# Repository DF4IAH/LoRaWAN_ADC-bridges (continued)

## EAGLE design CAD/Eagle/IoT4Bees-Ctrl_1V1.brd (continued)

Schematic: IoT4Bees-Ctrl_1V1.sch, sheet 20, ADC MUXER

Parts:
C2001, C2011, C2012, C2021, C2022, C2061, C2062, C2071, C2072: 100nF; C0402
L2011, L2012, L2021, L2022, L2061, L2062, L2071, L2072: 10uH; L0603
R2001, R2002, R2003, R2004: 0R; R0402
R2005, R2006: 22kR; R0402
R2011, R2012, R2021, R2022, R2061, R2062, R2071, R2072, R2090, R2091: 47R; R0402
U2011, U2012, U2021, U2022: TS5A23166; R-PDSO-G8

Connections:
+3V3_BRIDGE_PWR: C2001.1, R2005.2, R2006.2, U2011.8, U2012.8, U2021.8, U2022.8; also elsewhere on the board
ADC_MUX1_P1: C2011.1, L2011.1, R2001.2, U2011.1
ADC_MUX1_P1_L: L2011.2, R2011.1
ADC_MUX1_P5: C2061.1, L2061.1, R2002.2, U2011.5
ADC_MUX1_P5_L: L2061.2, R2061.1
ADC_MUX2_P1: C2021.1, L2021.2, R2003.1, U2021.1
ADC_MUX2_P1_L: L2021.1, R2021.2
ADC_MUX2_P5: C2071.1, L2071.2, R2004.1, U2021.5
ADC_MUX2_P5_L: L2071.1, R2071.2
ADC_MUX3_P1: C2012.1, L2012.1, U2012.1
ADC_MUX3_P1_L: L2012.2, R2012.1
ADC_MUX3_P5: C2062.1, L2062.1, U2012.5
ADC_MUX3_P5_L: L2062.2, R2062.1
ADC_MUX4_P1: C2022.1, L2022.2, U2022.1
ADC_MUX4_P1_L: L2022.1, R2022.2
ADC_MUX4_P5: C2072.1, L2072.2, U2022.5
ADC_MUX4_P5_L: L2072.1, R2072.2
ADC_MUX_GROUP0: R2090.2, U2011.3, U2011.7, U2021.3, U2021.7
ADC_MUX_GROUP1: R2091.2, U2012.3, U2012.7, U2022.3, U2022.7
ADC_VIN1N: R2002.1, U2011.6, U2012.6; also elsewhere on the board
ADC_VIN1P: R2001.1, R2005.1, U2011.2, U2012.2; also elsewhere on the board
ADC_VIN2N: R2004.2, U2021.6, U2022.6; also elsewhere on the board
ADC_VIN2P: R2003.2, R2006.1, U2021.2, U2022.2; also elsewhere on the board
BRIDGE_N1: R2061.2; also elsewhere on the board
BRIDGE_N2: R2071.1; also elsewhere on the board
BRIDGE_N3: R2062.2; also elsewhere on the board
BRIDGE_N4: R2072.1; also elsewhere on the board
BRIDGE_P1: R2011.2; also elsewhere on the board
BRIDGE_P2: R2021.1; also elsewhere on the board
BRIDGE_P3: R2012.2; also elsewhere on the board
BRIDGE_P4: R2022.1; also elsewhere on the board
GND: C2001.2, C2011.2, C2012.2, C2021.2, C2022.2, C2061.2, C2062.2, C2071.2, C2072.2, U2011.4, U2012.4, U2021.4, U2022.4; also elsewhere on the board
PH0: R2090.1; also elsewhere on the board
PH1: R2091.1; also elsewhere on the board

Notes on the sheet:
ADC MUXER for bridge input lines
ADC MUXER
GPIO_MUXG0_EN
GPIO_MUXG1_EN

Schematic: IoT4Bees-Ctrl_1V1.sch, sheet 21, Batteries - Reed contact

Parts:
BUZZER+: CUI Inc. CEB-44D06; SMD2,54-5,08
BUZZER-: CUI Inc. CEB-44D06; SMD2,54-5,08
C2111, C2132: 10pF; C0402
C2121: 10nF; C0402
L2111: 10uH; L0603
R2121: 1kR; R0402
S2131: REED-SWITCH-MK6-10; MK6-10
VIN+: 6V; SMD2,54-5,08
VIN-: 6V; SMD2,54-5,08

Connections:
+3V3: S2131.2; also elsewhere on the board
BUZZER: BUZZER+.1, R2121.1
GND: BUZZER-.1, C2111.2, C2121.2, C2132.2, VIN-.1; also elsewhere on the board
PA0: C2132.1, S2131.1; also elsewhere on the board
PB8: C2121.1, R2121.2; also elsewhere on the board
VBAT: L2111.2, VIN+.1
VBAT_L: C2111.1, L2111.1; also elsewhere on the board

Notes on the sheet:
Batteries connector
Batteries connector Reed contact
Reed contact
MCU_REED
Buzzer connector
TIM16_CH1_BUZZER

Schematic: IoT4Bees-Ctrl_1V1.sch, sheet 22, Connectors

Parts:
X2211, X2212: PHOENIX_1990067_1X8X2MM50_PTSA-0-5
X2251, X2252, X2253: HEADER-2X5_1MM27; 2X05_1MM27

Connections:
+3V3: X2251.3, X2251.9; also elsewhere on the board
+3V3_BRIDGE_PWR: X2211.1, X2211.5, X2212.1, X2212.5, X2251.4; also elsewhere on the board
+3V3_I2C1_PWR: X2251.6; also elsewhere on the board
+3V3_SPI3_PWR: X2251.5; also elsewhere on the board
+BAT_VOLTAGE_PWR: X2251.2; also elsewhere on the board
BRIDGE_N1: X2211.3; also elsewhere on the board
BRIDGE_N2: X2211.7; also elsewhere on the board
BRIDGE_N3: X2212.3; also elsewhere on the board
BRIDGE_N4: X2212.7; also elsewhere on the board
BRIDGE_P1: X2211.2; also elsewhere on the board
BRIDGE_P2: X2211.6; also elsewhere on the board
BRIDGE_P3: X2212.2; also elsewhere on the board
BRIDGE_P4: X2212.6; also elsewhere on the board
GND: X2211.4, X2211.8, X2212.4, X2212.8, X2251.10, X2252.10, X2253.10; also elsewhere on the board
PA1: X2253.8; also elsewhere on the board
PA2: X2253.9; also elsewhere on the board
PA5: X2252.9; also elsewhere on the board
PA6: X2252.8, X2253.7; also elsewhere on the board
PA7: X2252.7; also elsewhere on the board
PA9: X2252.2; also elsewhere on the board
PA10: X2252.1; also elsewhere on the board
PB1: X2253.5; also elsewhere on the board
PB10: X2253.1; also elsewhere on the board
PB11: X2253.2; also elsewhere on the board
PB13: X2253.6; also elsewhere on the board
PC0: X2253.4; also elsewhere on the board
PC1: X2253.3; also elsewhere on the board
PC2: X2252.3; also elsewhere on the board
PC3: X2252.4; also elsewhere on the board
PC4: X2252.5; also elsewhere on the board
PC13: X2252.6; also elsewhere on the board
PEXPA_P1_6_R: X2251.7; also elsewhere on the board
PEXPA_P1_7_R: X2251.8; also elsewhere on the board
VBAT_L: X2251.1; also elsewhere on the board

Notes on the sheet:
Connectors / Headers
BOARD_WKUP
Bridge Input Connectors
Expansion Connectors
SPI1_CLK
SPI1_MOSI
SPI1_MISO
SPI1_EXP_SEL
GPIO_EXTI2_EXPCON
GPIO_EXTI3_EXPCON
I2C1_SDA
I2C1_SCL
I2C2_SDA
I2C2_SCL
LPUART1_SIM_TX
LPUART1_SIM_RX
LPUART1_SIM_RTS
LPUART1_SIM_CTS
RCC_LSCO
ADC1_IN6_PEXP
TIM3_CH1_CAPT_PEXP
Bad connector spacing, library needs to be fixed

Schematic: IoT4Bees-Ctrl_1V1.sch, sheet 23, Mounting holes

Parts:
H2311, H2321, H2331, H2341: MOUNT-PAD-ROUND2.8; 2,8-PAD

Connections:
GND: H2311.B2,8, H2321.B2,8, H2331.B2,8, H2341.B2,8; also elsewhere on the board

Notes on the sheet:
Mounting holes
2x holes: diameters 7.00 mm and 3.50 mm on the PCB

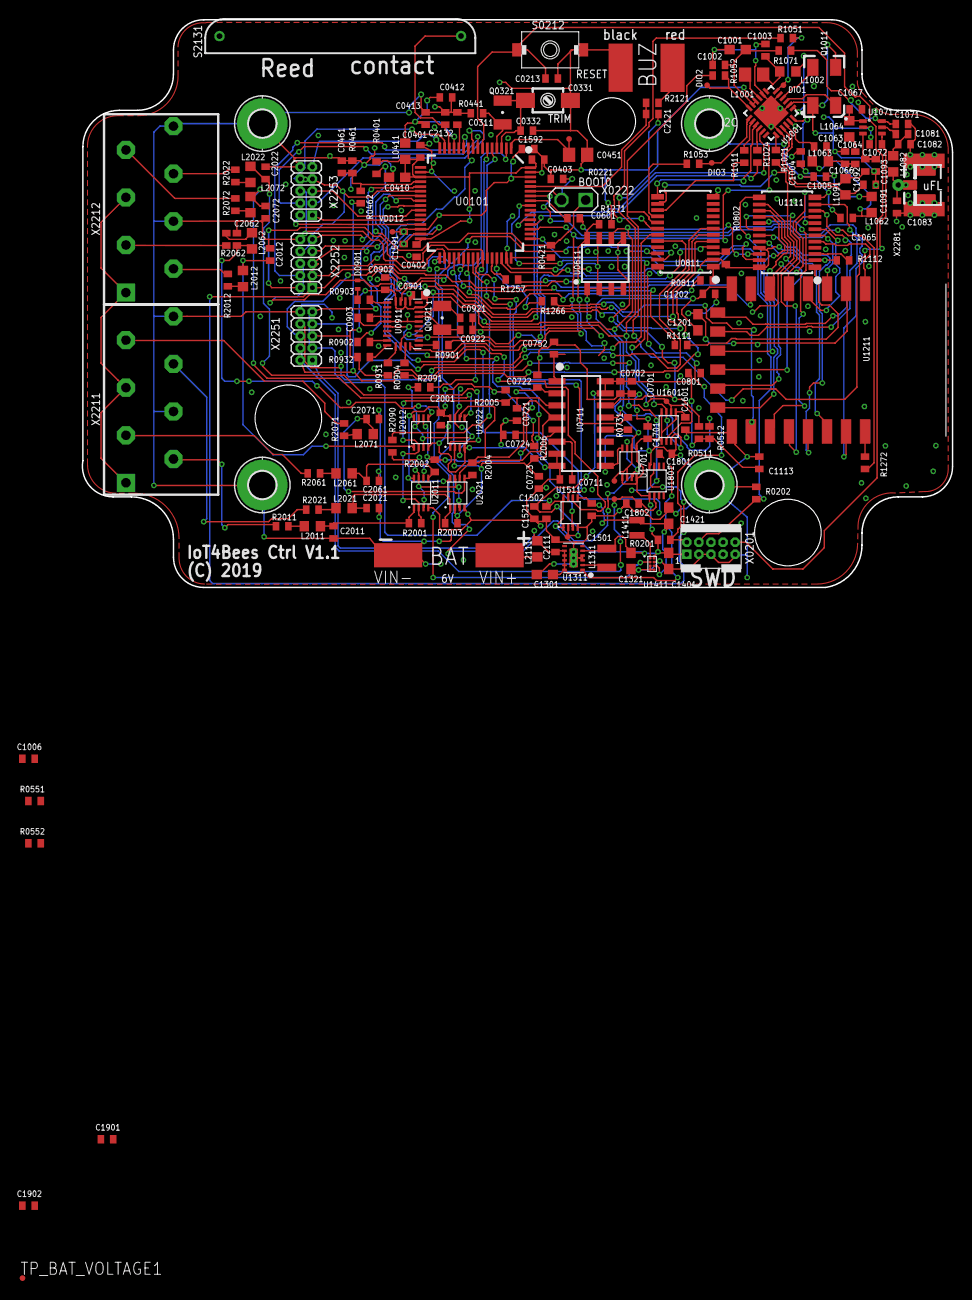
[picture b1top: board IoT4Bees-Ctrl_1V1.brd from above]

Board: 2 copper layers, 91.5 x 59.7 mm, 197 parts (0 on the bottom side), 164 nets.

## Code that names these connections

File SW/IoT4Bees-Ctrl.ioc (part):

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Mcu.Name=STM32L452RETxP
Mcu.Package=LQFP64
Mcu.UserName=STM32L452RETxP
PA0.GPIOParameters=GPIO_Label
PA0.GPIO_Label=REED_WKUP
PA0.Mode=SYS_WakeUp0
PA0.Signal=SYS_WKUP1
PA1.GPIOParameters=GPIO_Label
PA1.GPIO_Label=ADC1_IN6_PEXP
PA1.Signal=ADCx_IN6
PA10.GPIOParameters=GPIO_Speed,GPIO_PuPdOD
PA10.GPIO_PuPdOD=GPIO_NOPULL
PA10.GPIO_Speed=GPIO_SPEED_FREQ_HIGH
PA10.Mode=I2C
PA10.Signal=I2C1_SDA
PA11.GPIOParameters=GPIO_Speed,GPIO_PuPd,GPIO_Label
PA11.GPIO_Label=USART1_ESP_CTS
PA11.GPIO_PuPd=GPIO_PULLUP
PA11.GPIO_Speed=GPIO_SPEED_FREQ_MEDIUM
PA11.Signal=USART1_CTS
PA12.GPIOParameters=GPIO_Speed,GPIO_PuPd,GPIO_Label
PA12.GPIO_Label=USART1_ESP_RTS
PA12.GPIO_PuPd=GPIO_PULLUP
PA12.GPIO_Speed=GPIO_SPEED_FREQ_MEDIUM
PA12.Signal=USART1_RTS
PA13\ (JTMS/SWDIO).Mode=Serial_Wire
PA13\ (JTMS/SWDIO).Signal=SYS_JTMS-SWDIO
PA14\ (JTCK/SWCLK).Mode=Serial_Wire
PA14\ (JTCK/SWCLK).Signal=SYS_JTCK-SWCLK
PA2.Mode=Clock-out-LSCO
PA2.Signal=RCC_LSCO
PA4.GPIOParameters=GPIO_Label
PA4.GPIO_Label=ADC1_IN9_BAT
PA4.Signal=ADCx_IN9
PA6.GPIOParameters=GPIO_Label
PA6.GPIO_Label=TIM3_CH1_CAPT_PEXP
PA6.Signal=S_TIM3_CH1
PA8.GPIOParameters=GPIO_PuPd,GPIO_Label
PA8.GPIO_Label=GPIO_SW_I2C1_EN
PA8.GPIO_PuPd=GPIO_NOPULL
PA8.Signal=GPIO_Output
PA9.GPIOParameters=GPIO_Speed,GPIO_PuPdOD
PA9.GPIO_PuPdOD=GPIO_NOPULL
PA9.GPIO_Speed=GPIO_SPEED_FREQ_HIGH
PA9.Mode=I2C
PA9.Signal=I2C1_SCL
PB0.GPIOParameters=GPIO_PuPd,GPIO_Label
PB0.GPIO_Label=GPIO_SW_VOLTAGE_EN
PB0.GPIO_PuPd=GPIO_NOPULL
PB0.Signal=GPIO_Output
PB1.GPIOParameters=GPIO_Speed,GPIO_PuPd,GPIO_Label
PB1.GPIO_Label=LPUART1_SIM_RTS
PB1.GPIO_PuPd=GPIO_PULLUP
PB1.GPIO_Speed=GPIO_SPEED_FREQ_MEDIUM
PB1.Signal=LPUART1_RTS
PB10.GPIOParameters=GPIO_Speed,GPIO_PuPdOD
PB10.GPIO_PuPdOD=GPIO_PULLUP
PB10.GPIO_Speed=GPIO_SPEED_FREQ_HIGH
PB10.Mode=I2C
PB10.Signal=I2C2_SCL
PB11.GPIOParameters=GPIO_Speed,GPIO_PuPdOD
PB11.GPIO_PuPdOD=GPIO_PULLUP
PB11.GPIO_Speed=GPIO_SPEED_FREQ_HIGH
PB11.Mode=I2C
PB11.Signal=I2C2_SDA
PB12.GPIOParameters=GPIO_PuPd,GPIO_Label
PB12.GPIO_Label=GPIO_SW_USART1_EN
PB12.GPIO_PuPd=GPIO_NOPULL
PB12.Signal=GPIO_Output
PB13.GPIOParameters=GPIO_Speed,GPIO_PuPd,GPIO_Label
PB13.GPIO_Label=LPUART1_SIM_CTS
PB13.GPIO_PuPd=GPIO_PULLUP
PB13.GPIO_Speed=GPIO_SPEED_FREQ_MEDIUM
PB13.Signal=LPUART1_CTS
PB14.GPIOParameters=GPIO_PuPd,GPIO_Label
PB14.GPIO_Label=GPIO_SMPS_VDD12_EN
PB14.GPIO_PuPd=GPIO_NOPULL
PB14.Signal=GPIO_Output
PB15.GPIOParameters=GPIO_PuPd,GPIO_Label
PB15.GPIO_Label=GPIO_SW_VDD12_EN
PB15.GPIO_PuPd=GPIO_NOPULL
PB15.Signal=GPIO_Output
PB5.GPIOParameters=GPIO_PuPd,GPIO_Label
PB5.GPIO_Label=GPIO_SW_SPI3_EN
PB5.GPIO_PuPd=GPIO_NOPULL
PB5.Signal=GPIO_Output
PB6.GPIOParameters=GPIO_Speed,GPIO_Label
PB6.GPIO_Label=USART1_ESP_TX
PB6.GPIO_Speed=GPIO_SPEED_FREQ_MEDIUM
PB6.Mode=Asynchronous
PB6.Signal=USART1_TX
PB7.GPIOParameters=GPIO_Speed,GPIO_PuPd,GPIO_Label
PB7.GPIO_Label=USART1_ESP_RX
PB7.GPIO_PuPd=GPIO_PULLUP
PB7.GPIO_Speed=GPIO_SPEED_FREQ_MEDIUM
PB7.Mode=Asynchronous
PB7.Signal=USART1_RX
PB8.GPIOParameters=GPIO_Label
PB8.GPIO_Label=TIM16_CH1_BUZZER
PB8.Signal=S_TIM16_CH1
PC0.GPIOParameters=GPIO_Speed,GPIO_PuPd,GPIO_Label
PC0.GPIO_Label=LPUART1_SIM_RX
PC0.GPIO_PuPd=GPIO_PULLUP
PC0.GPIO_Speed=GPIO_SPEED_FREQ_MEDIUM
PC0.Mode=Asynchronous
PC0.Signal=LPUART1_RX
PC1.GPIOParameters=GPIO_Speed,GPIO_Label
PC1.GPIO_Label=LPUART1_SIM_TX
PC1.GPIO_Speed=GPIO_SPEED_FREQ_MEDIUM
PC1.Mode=Asynchronous
PC1.Signal=LPUART1_TX
PC10.Mode=Full_Duplex_Master
PC10.Signal=SPI3_SCK
PC11.GPIOParameters=GPIO_PuPd
PC11.GPIO_PuPd=GPIO_PULLDOWN
PC11.Mode=Full_Duplex_Master
PC11.Signal=SPI3_MISO
PC12.Mode=Full_Duplex_Master
PC12.Signal=SPI3_MOSI
PC13.GPIOParameters=GPIO_Label
PC13.GPIO_Label=BOARD_WKUP
PC13.Mode=SYS_WakeUp1
PC13.Signal=SYS_WKUP2
PC14-OSC32_IN\ (PC14).Mode=LSE-External-Oscillator
PC14-OSC32_IN\ (PC14).Signal=RCC_OSC32_IN
PC15-OSC32_OUT\ (PC15).Mode=LSE-External-Oscillator
PC15-OSC32_OUT\ (PC15).Signal=RCC_OSC32_OUT
PC2.GPIOParameters=GPIO_PuPd,GPIO_Label
PC2.GPIO_Label=GPIO_EXTI2_EXPCON
PC2.GPIO_PuPd=GPIO_PULLDOWN
PC2.Signal=GPXTI2
PC3.GPIOParameters=GPIO_PuPd,GPIO_Label
PC3.GPIO_Label=GPIO_EXTI3_EXPCON
PC3.GPIO_PuPd=GPIO_PULLDOWN
PC3.Signal=GPXTI3
PC4.GPIOParameters=GPIO_PuPd,GPIO_Label
PC4.GPIO_Label=GPIO_SW_BRIDGE_EN
PC4.GPIO_PuPd=GPIO_NOPULL
PC4.Signal=GPIO_Output
PC7.GPIOParameters=GPIO_PuPd,GPIO_Label,GPIO_ModeDefaultEXTI
PC7.GPIO_Label=EXTI7_I2C1_PEXPB
PC7.GPIO_ModeDefaultEXTI=GPIO_MODE_IT_FALLING
PC7.GPIO_PuPd=GPIO_PULLUP
PC7.Signal=GPXTI7
PC8.GPIOParameters=GPIO_PuPd,GPIO_Label,GPIO_ModeDefaultEXTI
PC8.GPIO_Label=EXTI8_I2C1_PEXPA
PC8.GPIO_ModeDefaultEXTI=GPIO_MODE_IT_FALLING
PC8.GPIO_PuPd=GPIO_PULLUP
PC8.Signal=GPXTI8
PC9.GPIOParameters=GPIO_PuPd,GPIO_Label
PC9.GPIO_Label=EXTI9_I2C1_ADC_DRDY
PC9.GPIO_PuPd=GPIO_PULLDOWN
PC9.Signal=GPXTI9
PH0-OSC_IN\ (PH0).GPIOParameters=GPIO_PuPd,GPIO_Label
PH0-OSC_IN\ (PH0).GPIO_Label=GPIO_MUXG0_EN
PH0-OSC_IN\ (PH0).GPIO_PuPd=GPIO_NOPULL
PH0-OSC_IN\ (PH0).Signal=GPIO_Output
PH1-OSC_OUT\ (PH1).GPIOParameters=GPIO_PuPd,GPIO_Label
PH1-OSC_OUT\ (PH1).GPIO_Label=GPIO_MUXG1_EN
PH1-OSC_OUT\ (PH1).GPIO_PuPd=GPIO_NOPULL
PH1-OSC_OUT\ (PH1).Signal=GPIO_Output
RCC.HSE_VALUE=8000000
RCC.SYSCLKFreq_VALUE=16000000
board=custom

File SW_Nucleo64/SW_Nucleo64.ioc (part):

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Mcu.Name=STM32L452RETxP
Mcu.Package=LQFP64
Mcu.UserName=STM32L452RETxP
PA0.GPIOParameters=GPIO_Label
PA0.GPIO_Label=REED_WKUP
PA0.Mode=SYS_WakeUp0
PA0.Signal=SYS_WKUP1
PA10.Mode=I2C
PA10.Signal=I2C1_SDA
PA11.GPIOParameters=GPIO_Label
PA11.GPIO_Label=USART1_ESP_CTS
PA11.Mode=CTS_RTS
PA11.Signal=USART1_CTS
PA12.GPIOParameters=GPIO_Label
PA12.GPIO_Label=USART1_ESP_RTS
PA12.Mode=CTS_RTS
PA12.Signal=USART1_RTS
PA13\ (JTMS/SWDIO).GPIOParameters=GPIO_Label
PA13\ (JTMS/SWDIO).GPIO_Label=TMS
PA13\ (JTMS/SWDIO).Mode=Serial_Wire
PA13\ (JTMS/SWDIO).Signal=SYS_JTMS-SWDIO
PA14\ (JTCK/SWCLK).GPIOParameters=GPIO_Label
PA14\ (JTCK/SWCLK).GPIO_Label=TCK
PA14\ (JTCK/SWCLK).Mode=Serial_Wire
PA14\ (JTCK/SWCLK).Signal=SYS_JTCK-SWCLK
PA2.GPIOParameters=GPIO_Speed,GPIO_PuPd,GPIO_Label,GPIO_Mode
PA2.GPIO_Label=USART_TX
PA2.GPIO_Mode=GPIO_MODE_AF_PP
PA2.GPIO_PuPd=GPIO_NOPULL
PA2.GPIO_Speed=GPIO_SPEED_FREQ_VERY_HIGH
PA2.Mode=Asynchronous
PA2.Signal=USART2_TX
PA3.GPIOParameters=GPIO_Speed,GPIO_PuPd,GPIO_Label,GPIO_Mode
PA3.GPIO_Label=USART_RX
PA3.GPIO_Mode=GPIO_MODE_AF_PP
PA3.GPIO_PuPd=GPIO_NOPULL
PA3.GPIO_Speed=GPIO_SPEED_FREQ_VERY_HIGH
PA3.Mode=Asynchronous
PA3.Signal=USART2_RX
PA4.GPIOParameters=GPIO_Label
PA4.GPIO_Label=SMPS_EN [ADP5301ACBZ_VEN]
PA4.Signal=GPIO_Output
PA5.GPIOParameters=GPIO_Speed,GPIO_PuPd,GPIO_Label,GPIO_ModeDefaultOutputPP
PA5.GPIO_Label=SMPS_V1
PA5.GPIO_ModeDefaultOutputPP=GPIO_MODE_OUTPUT_PP
PA5.GPIO_PuPd=GPIO_NOPULL
PA5.GPIO_Speed=GPIO_SPEED_FREQ_LOW
PA5.Signal=GPIO_Output
PA6.GPIOParameters=GPIO_PuPd,GPIO_Label
PA6.GPIO_Label=SMPS_PG [ADP5301ACBZ_OUTOK]
PA6.GPIO_PuPd=GPIO_PULLUP
PA6.Signal=GPIO_Input
PA7.GPIOParameters=GPIO_Label
PA7.GPIO_Label=SMPS_SW [TS3A44159PWR_IN1_2]
PA7.Signal=GPIO_Output
PA8.Mode=Clock-out
PA8.Signal=RCC_MCO
PA9.Mode=I2C
PA9.Signal=I2C1_SCL
PB0.GPIOParameters=GPIO_Label
PB0.GPIO_Label=GPIO_SW_VOLTAGE_EN
PB0.Signal=GPIO_Output
PB12.GPIOParameters=GPIO_Label
PB12.GPIO_Label=GPIO_SW_USART1_EN
PB12.Signal=GPIO_Output
PB13.GPIOParameters=GPIO_Label
PB13.GPIO_Label=LD4 [green Led]
PB13.Signal=GPIO_Output
PB3\ (JTDO/TRACESWO).GPIOParameters=GPIO_Label
PB3\ (JTDO/TRACESWO).GPIO_Label=SWO
PB3\ (JTDO/TRACESWO).Signal=SYS_JTDO-SWO
PB5.GPIOParameters=GPIO_Label
PB5.GPIO_Label=GPIO_SW_SPI3_EN
PB5.Signal=GPIO_Output
PB6.GPIOParameters=GPIO_Label
PB6.GPIO_Label=USART1_ESP_TX
PB6.Mode=Asynchronous
PB6.Signal=USART1_TX
PB7.GPIOParameters=GPIO_Label
PB7.GPIO_Label=USART1_ESP_RX
PB7.Mode=Asynchronous
PB7.Signal=USART1_RX
PB8.GPIOParameters=GPIO_Label
PB8.GPIO_Label=TIM16_CH1_BUZZER
PB8.Signal=S_TIM16_CH1
PC10.Mode=Full_Duplex_Master
PC10.Signal=SPI3_SCK
PC11.Mode=Full_Duplex_Master
PC11.Signal=SPI3_MISO
PC12.Mode=Full_Duplex_Master
PC12.Signal=SPI3_MOSI
PC13.GPIOParameters=GPIO_PuPd,GPIO_Label,GPIO_ModeDefaultEXTI
PC13.GPIO_Label=B1 [Blue PushButton]
PC13.GPIO_ModeDefaultEXTI=GPIO_MODE_IT_FALLING
PC13.GPIO_PuPd=GPIO_NOPULL
PC13.Signal=GPXTI13
PC14-OSC32_IN\ (PC14).Mode=LSE-External-Oscillator
PC14-OSC32_IN\ (PC14).Signal=RCC_OSC32_IN
PC15-OSC32_OUT\ (PC15).Mode=LSE-External-Oscillator
PC15-OSC32_OUT\ (PC15).Signal=RCC_OSC32_OUT
PC4.GPIOParameters=GPIO_Label
PC4.GPIO_Label=GPIO_SW_BRIDGE_EN
PC4.Signal=GPIO_Output
PC7.GPIOParameters=GPIO_Label
PC7.GPIO_Label=EXTI7_I2C1_PEXPB
PC7.Signal=GPXTI7
PC8.GPIOParameters=GPIO_Label
PC8.GPIO_Label=EXTI8_I2C1_PEXPA
PC8.Signal=GPXTI8
PC9.GPIOParameters=GPIO_Label
PC9.GPIO_Label=EXTI9_I2C1_ADC_DRDY
PC9.Signal=GPXTI9
PH0-OSC_IN\ (PH0).GPIOParameters=GPIO_Label
PH0-OSC_IN\ (PH0).GPIO_Label=MCO
PH0-OSC_IN\ (PH0).Signal=RCC_OSC_IN
PH1-OSC_OUT\ (PH1).Signal=RCC_OSC_OUT
RCC.HSE_VALUE=8000000
RCC.SYSCLKFreq_VALUE=16000000
RCC.SYSCLKSource=RCC_SYSCLKSOURCE_HSI
board=NUCLEO-L452RE-P
boardIOC=true

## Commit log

2020-01-02 Complete copy from IoT4Bees-Ctrl w/o SW-tools
2020-01-02 Docs - _HISTORIC__Logs - added
2020-01-02 SW - rename project files
2020-01-02 SW - update to IDE 5.4.0 and Libs keeping 1.14.0
2020-01-02 SW - repair IDE upgrade
2020-01-02 SW - ADC - interrupt handling enhanced
2020-03-25 Upgrade to MCU 1.15.1
